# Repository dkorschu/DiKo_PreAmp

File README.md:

# $\text{-DIKO-}\sqrt{\text{REGGAE}}\text{-PREAMP-}$

[English version below](#english-version)

Dieses Repository zeigt die Entwicklung des DIKO ELEKTROTECHNIK Vorverstärkers, vom ersten Prototyp bis zum aktuellen Stand.

## Ordnerstruktur

- Blockschaltbilder
- Ältere Versionen
- KiCad Dateien
- Bilder
- Datenblätter
- 3D Druck

## Version 1

Version 1 entstand im Rahmen meiner Bachelorarbeit. Schaltpläne und Fertigungsdateien der Platinen wurden mit Altium Designer erstellt. Das Besondere an dieser Version: Die analoge Frequenzweiche lässt sich über Digitalpotentiometer einstellen.

**Hinweis: Version 1 ist fehlerhaft!**

## Version 2

Version 2 baut auf den Erkenntnissen aus Version 1 auf und bringt komplett neue Platinen mit. Die Digitalpotentiometer sind entfallen, da der Vorverstärker einfacher werden und der Fokus zunächst auf der analogen Schaltungstechnik liegen sollte. Zur Berechnung der Frequenzweiche wurden außerdem Jupyter Notebooks eingesetzt, die sehr gute Ergebnisse geliefert haben.

Bei den bisherigen Tests wurden schaltungstechnisch keine Fehler gefunden. Trotzdem gibt es zwei Schwachstellen:

- Das Platinenlayout ist nicht zufriedenstellend.
- Der Mikrofonvorverstärker verstärkt das Signal nicht ausreichend.

Aus diesen Gründen wird nun an Version 3 gearbeitet.

## Version 3

Version 3 teilt den Vorverstärker in einzelne Komponenten auf, die sich miteinander verbinden lassen.

2026_10_05 Den Anfang macht die Frequenzweiche, die sich auch eigenständig mit einem externen Mischpult nutzen lässt.

---

# English Version

This repository documents the development of the DIKO ELEKTROTECHNIK preamplifier, from the first prototype to the current state.

## Folder Structure

- Blockschaltbilder (block diagrams)
- Ältere Versionen (older versions)
- KiCad Dateien (KiCad files)
- Bilder (images)
- Datenblätter (datasheets)
- 3D Druck (3D printing)

## Version 1
Version 1 was developed as part of my bachelor's thesis. The schematics and PCB manufacturing files were created with Altium Designer. What makes this version special: the analog crossover can be adjusted using digital potentiometers.

**Note: Version 1 is faulty!**

## Version 2

Version 2 builds on the findings from Version 1 and comes with completely new PCBs. The digital potentiometers were removed to make the preamp simpler and to focus on the analog circuitry first. In addition, Jupyter Notebooks were used to calculate the crossover, with very good results.

So far, testing has not revealed any circuit errors. However, there are two weak points:

- The PCB layout is not satisfactory.
- The microphone preamp does not amplify the signal sufficiently.

For these reasons, work is now underway on Version 3.

## Version 3

Version 3 splits the preamp into individual components that can be connected to each other.

2026_10_05 The first step is the crossover, which can also be used on its own with an external mixing console.

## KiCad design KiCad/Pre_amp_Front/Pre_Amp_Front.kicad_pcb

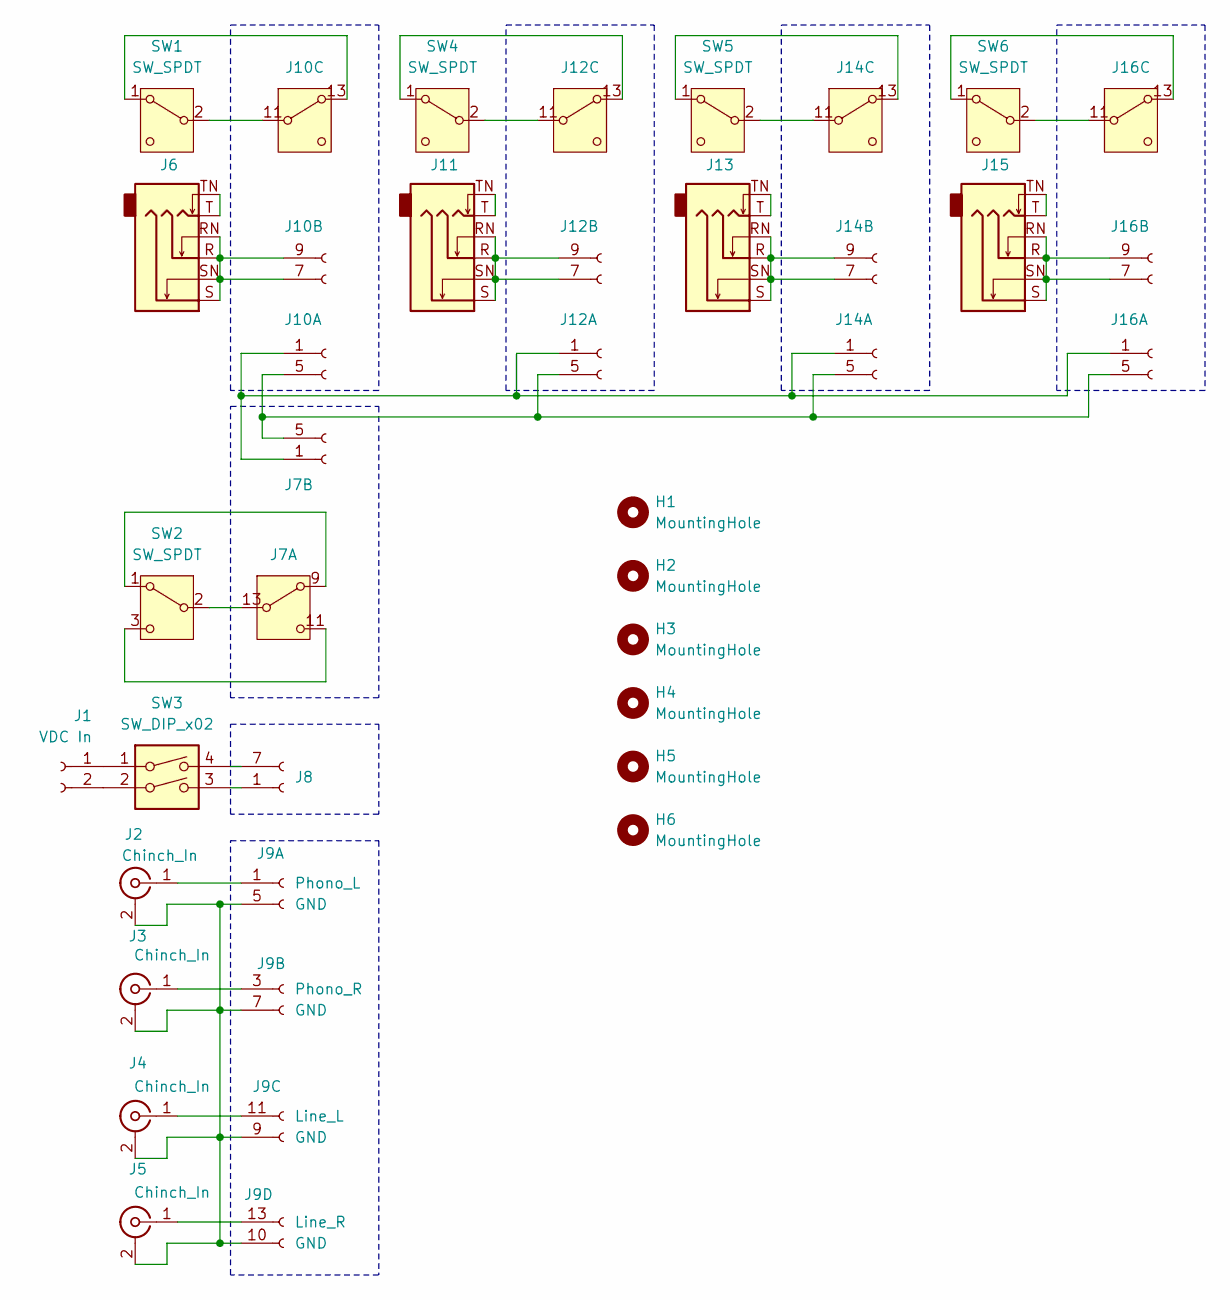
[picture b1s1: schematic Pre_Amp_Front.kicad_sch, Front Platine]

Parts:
H1, H2, H3, H4, H5, H6: MountingHole; MountingHole_3.2mm_M3
J1: VDC In; Chinch_lose
J2, J3, J4, J5: Chinch_In; Chinch_lose
J6, J11, J13, J15: NRJ6HF; Jack_6.35mm_Neutrik_NMJ6HFD3_Horizontal
J7: Stecker_1Out_Switch; PinHeader_2x07_P2.54mm_Vertical
J8: Stecker_2x7_VDC; PinHeader_2x07_P2.54mm_Vertical
J9: Stecker_4In; PinHeader_2x07_P2.54mm_Vertical
J10, J12, J14, J16: Stecker_In_Out_Switch; PinHeader_2x07_P2.54mm_Vertical
SW1, SW4, SW5, SW6: SW_SPDT; Chinch_lose
SW2: SW_SPDT; Schalter_3x_lose
SW3: SW_DIP_x02; Schalter_4x_lose

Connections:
unnamed: J1.1, SW3.1
unnamed: J1.2, SW3.2
unnamed: J2.2 (Ext), J3.2 (Ext), J4.2 (Ext), J5.2 (Ext), J9.5 (GND), J9.6 (GND), J9.7 (GND), J9.8 (GND), J9.9 (GND), J9.10 (GND)
unnamed: J2.1 (In), J9.1 (Phono_L), J9.2
unnamed: J3.1 (In), J9.3 (Phono_R), J9.4 (Phono_R)
unnamed: J4.1 (In), J9.11 (Line_L), J9.12 (Line_L)
unnamed: J5.1 (In), J9.13 (Line_R), J9.14 (Line_R)
unnamed: J6.T, J6.TN
unnamed: J7.9 (SW_In1), J7.10 (SW_2), SW2.1 (A)
unnamed: J7.11 (SW_In2), J7.12 (SW_3), SW2.3 (C)
unnamed: J8.7 (VCC_GND), J8.8 (VCC_GND), J8.9 (VCC_GND), J8.10 (VCC_GND), J8.11 (VCC_GND), J8.12 (VCC_GND), J8.13 (VCC_GND), J8.14 (VCC_GND), SW3.4
unnamed: J8.1 (VCC_In), J8.2 (VCC_In), J8.3 (VCC_In), J8.4 (VCC_In), J8.5 (VCC_In), J8.6 (VCC_In), SW3.3
unnamed: J7.1 (Out), J7.2 (Out), J10.1, J10.2, J12.1, J12.2, J14.1, J14.2, J16.1, J16.2
unnamed: J7.3 (GND), J7.4 (GND), J7.5 (GND), J7.6 (GND), J7.7 (GND), J7.8 (GND), J10.3, J10.4, J10.5, J10.6, J12.3, J12.4, J12.5, J12.6, J14.3, J14.4, J14.5, J14.6, J16.3, J16.4, J16.5, J16.6
unnamed: J6.R, J6.RN, J6.S, J6.SN, J10.7, J10.8, J10.9, J10.10
unnamed: J10.11 (SW_In), J10.12, SW1.2 (B)
unnamed: J10.13 (SW_Out), J10.14, SW1.1 (A)
unnamed: J11.T, J11.TN
unnamed: J11.R, J11.RN, J11.S, J11.SN, J12.7, J12.8, J12.9, J12.10
unnamed: J12.11 (SW_In), J12.12, SW4.2 (B)
unnamed: J12.13 (SW_Out), J12.14, SW4.1 (A)
unnamed: J13.T, J13.TN
unnamed: J13.R, J13.RN, J13.S, J13.SN, J14.7, J14.8, J14.9, J14.10
unnamed: J14.11 (SW_In), J14.12, SW5.2 (B)
unnamed: J14.13 (SW_Out), J14.14, SW5.1 (A)
unnamed: J15.T, J15.TN
unnamed: J15.R, J15.RN, J15.S, J15.SN, J16.7, J16.8, J16.9, J16.10
unnamed: J16.11 (SW_In), J16.12, SW6.2 (B)
unnamed: J16.13 (SW_Out), J16.14, SW6.1 (A)
unnamed: J7.13 (SW_Out), J7.14 (SW_Out), SW2.2 (B)

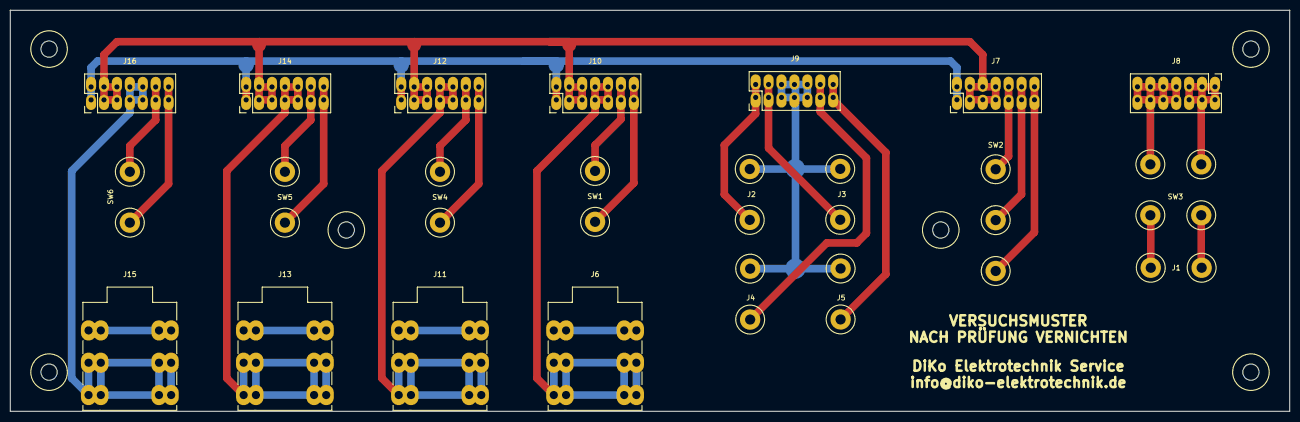
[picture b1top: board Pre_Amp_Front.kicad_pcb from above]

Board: 2 copper layers, 251.5 x 78.8 mm, 28 parts (0 on the bottom side), 30 nets.

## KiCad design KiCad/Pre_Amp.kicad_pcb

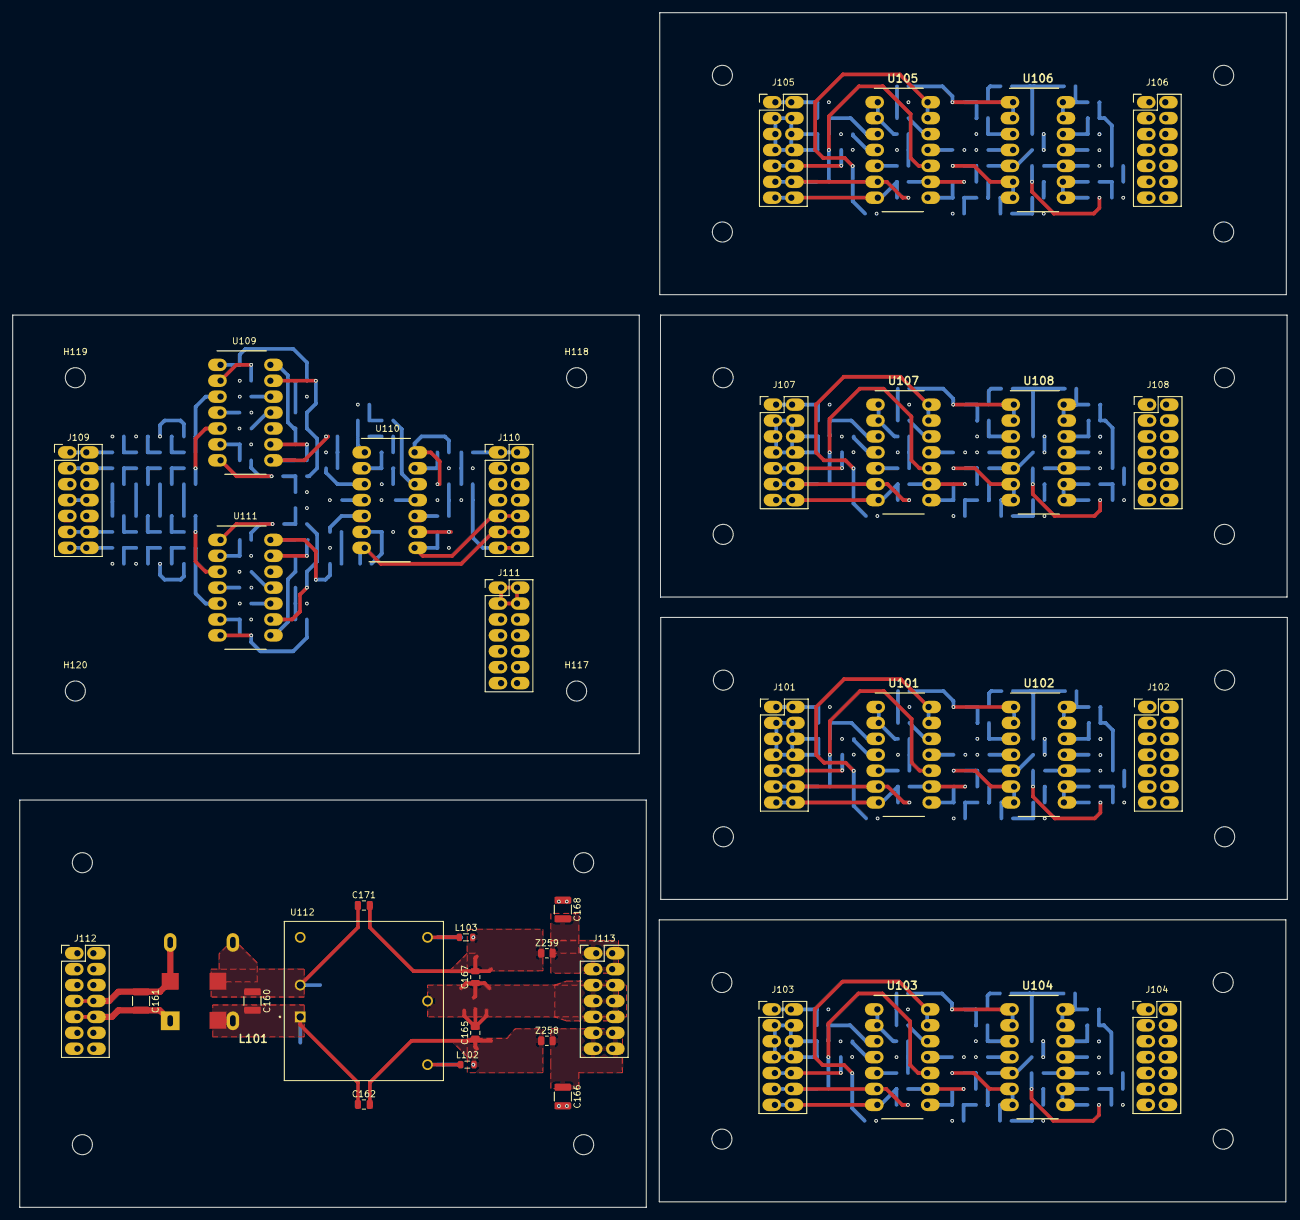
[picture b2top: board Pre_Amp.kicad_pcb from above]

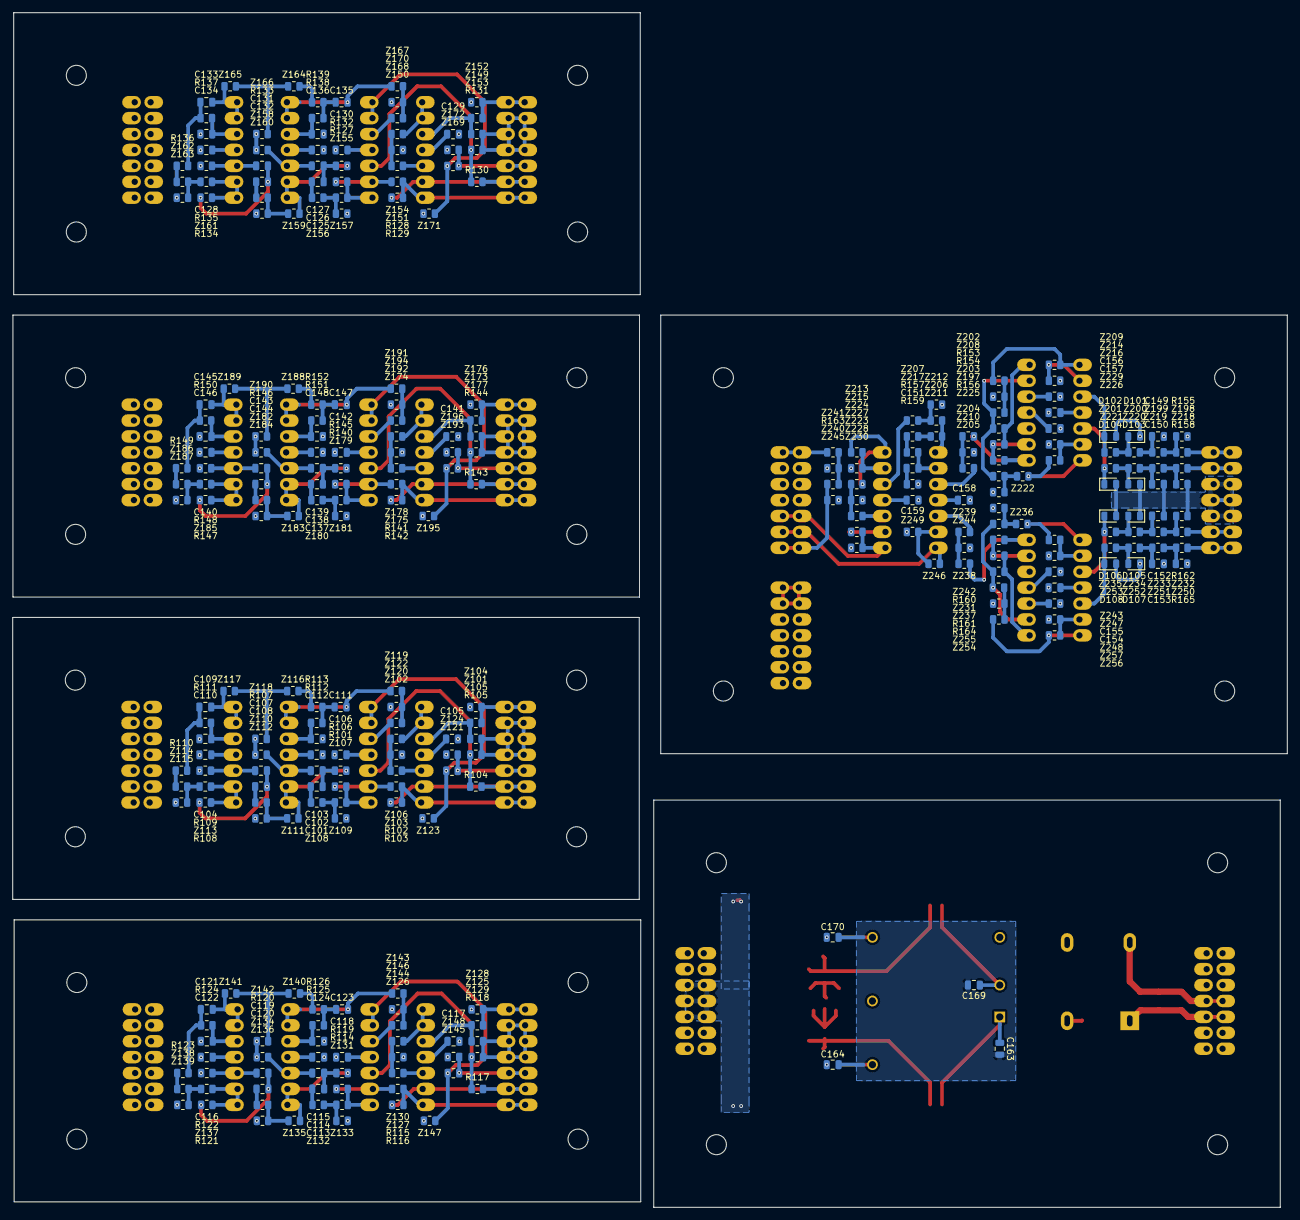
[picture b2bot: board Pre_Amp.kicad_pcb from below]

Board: 4 copper layers, 203.4 x 190.7 mm, 355 parts (293 on the bottom side), 210 nets.

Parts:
C101, C102, C113, C114, C125, C126, C137, C138, C149, C150, C152, C153, C163, C169: 10n; C_0805_2012Metric
C103, C104, C105, C106, C112, C115, C116, C117, C118, C124, C127, C128, C129, C130, C136, C139, C140, C141, C142, C148, C154, C155, C156, C157, C158, C159, C165, C167: 100n; C_0805_2012Metric
C107, C108, C119, C120, C131, C132, C143, C144: 220n; C_0805_2012Metric
C109, C110, C121, C122, C133, C134, C145, C146: 150n; C_0805_2012Metric
C111, C123, C135, C147: 1u; C_0805_2012Metric
C151: 47u; C_0805_2012Metric
C160, C161, C166, C168: 10u; C_1210_3225Metric
C162, C171: 470p; C_0805_2012Metric
C164, C170: 1n; C_0805_2012Metric
D101, D102, D103, D104, D105, D106, D107, D108: D; D_0805_2012Metric
H101, H102, H103, H104, H105, H106, H107, H108, H109, H110, H111, H112, H113, H114, H115, H116, H117, H118, H119, H120, H121, H122, H123, H124: MountingHole; MountingHole_3.2mm_M3
J101, J103, J105, J107: Stecker_In_Out_Switch; PinHeader_2x07_P2.54mm_Vertical
J102, J104, J106, J108, J111: Conn_02x07_Odd_Even; PinHeader_2x07_P2.54mm_Vertical
J109: Stecker_4In; PinHeader_2x07_P2.54mm_Vertical
J110: Stecker_1Out_Switch; PinHeader_2x07_P2.54mm_Vertical
J112: Stecker_1In_2Switch; PinHeader_2x07_P2.54mm_Vertical
J113: VCC; PinHeader_2x07_P2.54mm_Vertical
L101: WE-SL575
L102, L103: Dämpfungsperle, 220 Ohm @ 100MHz, 0.5A; L_0805_2012Metric
R101, R105, R114, R118, R127, R131, R140, R144: 100k; R_0805_2012Metric
R102, R103, R104, R115, R116, R117, R128, R129, R130, R141, R142, R143, R159: 1k; R_0805_2012Metric
R106, R119, R132, R145: 560k; R_0805_2012Metric
R107, R120, R133, R146: 680k; R_0805_2012Metric
R108, R121, R134, R147, R153, R154, R156, R160, R161, R164: 10k; R_0805_2012Metric
R109, R122, R135, R148: 75k; R_0805_2012Metric
R110, R111, R123, R124, R136, R137, R149, R150: 15k; R_0805_2012Metric
R112, R113, R125, R126, R138, R139, R151, R152: 7k5; R_0805_2012Metric
R155, R158, R162, R163, R165: 390k; R_0805_2012Metric
R157: 33k; R_0805_2012Metric
U101, U102, U103, U104, U105, U106, U107, U108, U109, U110, U111: TL074; DIP794W53P254L1930H508Q14N
U112: REC10K-2415; CONV_REC10K-2415DAW_H2
Z101, Z121, Z125, Z145, Z149, Z169, Z173, Z193: 1u; R_0805_2012Metric
Z102, Z103, Z107, Z108, Z110, Z111, Z113, Z114, Z116, Z117, Z119, Z120, Z126, Z127, Z131, Z132, Z134, Z135, Z137, Z138, Z140, Z141, Z143, Z144, Z150, Z151, Z155, Z156, Z158, Z159, Z161, Z162, Z164, Z165, Z167, Z168, Z174, Z175, Z179, Z180, Z182, Z183, Z185, Z186, Z188, Z189, Z191, Z192, Z204, Z205, Z206, Z207, Z223, Z224, Z238, Z239, Z258, Z259: 0R; R_0805_2012Metric
Z104, Z106, Z109, Z112, Z118, Z123, Z128, Z130, Z133, Z136, Z142, Z147, Z152, Z154, Z157, Z160, Z166, Z171, Z176, Z178, Z181, Z184, Z190, Z195, Z197, Z198, Z199, Z200, Z201, Z202, Z203, Z208, Z209, Z213, Z214, Z215, Z216, Z218, Z219, Z220, Z221, Z222, Z225, Z226, Z228, Z229, Z230, Z231, Z232, Z233, Z234, Z235, Z236, Z237, Z240, Z241, Z242, Z243, Z245, Z246, Z247, Z248, Z249, Z250, Z251, Z252, Z253, Z254, Z255, Z256, Z257: R_0805_2012Metric
Z105, Z124, Z129, Z148, Z153, Z172, Z177, Z196: 100k; R_0805_2012Metric
Z115, Z122, Z139, Z146, Z163, Z170, Z187, Z194, Z210, Z212, Z227, Z244: 820k; R_0805_2012Metric
Z211: 390k/10n; R_0805_2012Metric
Z217: 33k/2n2; R_0805_2012Metric

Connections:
+15V: C103.2, C105.2, C115.2, C117.2, C127.2, C129.2, C139.2, C141.2, C154.2, C156.2, C158.2, C166.1, J102.11, J102.12, J102.13, J102.14, J104.11, J104.12, J104.13, J104.14, J106.11, J106.12, J106.13, J106.14, J108.11, J108.12, J108.13, J108.14, J111.11, J111.12, J111.13, J111.14, J113.11 (+15V), J113.12 (+15V), J113.13 (+15V), J113.14 (+15V), U101.4 (V+), U102.4 (V+), U103.4 (V+), U104.4 (V+), U105.4 (V+), U106.4 (V+), U107.4 (V+), U108.4 (V+), U109.4 (V+), U110.4 (V+), U111.4 (V+), Z258.2
-15V: C104.2, C106.2, C116.2, C118.2, C128.2, C130.2, C140.2, C142.2, C155.2, C157.2, C159.2, C168.2, J102.1, J102.2, J102.3, J102.4, J104.1, J104.2, J104.3, J104.4, J106.1, J106.2, J106.3, J106.4, J108.1, J108.2, J108.3, J108.4, J111.1, J111.2, J111.3, J111.4, J113.1 (-15V), J113.2 (-15V), J113.3 (-15V), J113.4 (-15V), U101.11 (V-), U102.11 (V-), U103.11 (V-), U104.11 (V-), U105.11 (V-), U106.11 (V-), U107.11 (V-), U108.11 (V-), U109.11 (V-), U110.11 (V-), U111.11 (V-), Z259.2
GND: C103.1, C104.1, C105.1, C106.1, C110.1, C112.1, C115.1, C116.1, C117.1, C118.1, C122.1, C124.1, C127.1, C128.1, C129.1, C130.1, C134.1, C136.1, C139.1, C140.1, C141.1, C142.1, C146.1, C148.1, C149.1, C150.1, C152.1, C153.1, C154.1, C155.1, C156.1, C157.1, C158.1, C159.1, C165.2, C166.2, C167.1, C168.1, D101.1 (K), D102.2 (A), D103.1 (K), D104.2 (A), D105.1 (K), D106.2 (A), D107.1 (K), D108.2 (A), J101.3, J101.4, J101.5, J101.6, J101.7, J101.8, J102.5, J102.6, J102.7, J102.8, J102.9, J102.10, J103.3, J103.4, J103.5, J103.6, J103.7, J103.8, J104.5, J104.6, J104.7, J104.8, J104.9, J104.10, J105.3, J105.4, J105.5, J105.6, J105.7, J105.8, J106.5, J106.6, J106.7, J106.8, J106.9, J106.10, J107.3, J107.4, J107.5, J107.6, J107.7, J107.8, J108.5, J108.6, J108.7, J108.8, J108.9, J108.10, J109.5 (GND), J109.6 (GND), J109.7 (GND), J109.8 (GND), J109.9 (GND), J109.10 (GND), J110.3 (GND), J110.4 (GND), J110.5 (GND), J110.6 (GND), J110.7 (GND), J110.8 (GND), J111.5, J111.6, J111.7, J111.8, J111.9, J111.10, J113.5 (GND), J113.6 (GND), J113.7 (GND), J113.8 (GND), J113.9 (GND), J113.10 (GND), R105.1, R107.1, R109.1, R118.1, R120.1, R122.1, R131.1, R133.1, R135.1, R144.1, R146.1, R148.1, R155.2, R158.2, R159.1, R162.2, R163.2, R165.2, U109.10 (+), U111.12 (+), U112.5 (COM), Z104.2, Z105.2, Z106.2, Z109.2, Z112.2, Z115.2, Z118.2, Z122.2, Z123.2, Z124.2, Z128.2, Z129.2, Z130.2, Z133.2, Z136.2, Z139.2, Z142.2, Z146.2, Z147.2, Z148.2, Z152.2, Z153.2, Z154.2, Z157.2, Z160.2, Z163.2, Z166.2, Z170.2, Z171.2, Z172.2, Z176.2, Z177.2, Z178.2, Z181.2, Z184.2, Z187.2, Z190.2, Z194.2, Z195.2, Z196.2, Z208.2, Z210.2, Z212.2, Z214.2, Z215.2, Z216.2, Z225.2, Z227.2, Z229.2, Z230.2, Z242.2, Z244.2, Z245.2, Z247.2, Z248.2, Z249.2, Z255.2, Z257.2
GND_FILT: C163.2, C164.2, C169.2, C170.2
unnamed: C101.1, Z108.1
unnamed: C101.2, C102.1, R106.1
unnamed: C107.1, C108.2, R108.1
unnamed: C108.1, Z110.2
unnamed: C109.1, R110.2, R111.1
unnamed: C111.1, R112.1, R113.2
unnamed: C113.1, Z132.1
unnamed: C113.2, C114.1, R119.1
unnamed: C119.1, C120.2, R121.1
unnamed: C120.1, Z134.2
unnamed: C121.1, R123.2, R124.1
unnamed: C123.1, R125.1, R126.2
unnamed: C125.1, Z156.1
unnamed: C125.2, C126.1, R132.1
unnamed: C131.1, C132.2, R134.1
unnamed: C132.1, Z158.2
unnamed: C133.1, R136.2, R137.1
unnamed: C135.1, R138.1, R139.2
unnamed: C137.1, Z180.1
unnamed: C137.2, C138.1, R145.1
unnamed: C143.1, C144.2, R147.1
unnamed: C144.1, Z182.2
unnamed: C145.1, R149.2, R150.1
unnamed: C147.1, R151.1, R152.2
unnamed: C149.2, Z199.2, Z200.1
unnamed: C150.2, Z219.2, Z220.1
unnamed: C151.1, R159.2
unnamed: C152.2, Z233.2, Z234.1
unnamed: C153.2, Z251.2, Z252.1
unnamed: C161.1, J112.7 (SW_2), J112.8 (SW_2), L101.4
unnamed: C161.2, J112.9 (SW_4), J112.10 (SW_4), L101.1
unnamed: C162.2, C164.1, C165.1, L102.2, Z258.1
unnamed: C167.2, C170.1, C171.2, L103.2, Z259.1
unnamed: D101.2 (A), Z200.2, Z201.1
unnamed: D102.1 (K), U109.3 (+), Z201.2
unnamed: D103.2 (A), Z220.2, Z221.1
unnamed: D104.1 (K), U109.5 (+), Z221.2
unnamed: D105.2 (A), Z234.2, Z235.1
unnamed: D106.1 (K), U111.3 (+), Z235.2
unnamed: D107.2 (A), Z252.2, Z253.1
unnamed: D108.1 (K), U111.5 (+), Z253.2
unnamed: J101.1, J101.2, J103.1, J103.2, J105.1, J105.2, J107.1, J107.2, J110.1 (Out), J110.2 (Out), Z101.2, Z104.1, Z125.2, Z128.1, Z149.2, Z152.1, Z173.2, Z176.1, Z241.1
unnamed: J101.9, J101.10, Z121.2, Z124.1
unnamed: J101.11 (SW_In), J101.12, R103.1, R104.1, U101.6 (-)
unnamed: J101.13 (SW_Out), J101.14, R102.1, R103.2, U101.7
unnamed: J103.9, J103.10, Z145.2, Z148.1
unnamed: J103.11 (SW_In), J103.12, R116.1, R117.1, U103.6 (-)
unnamed: J103.13 (SW_Out), J103.14, R115.1, R116.2, U103.7
unnamed: J105.9, J105.10, Z169.2, Z172.1
unnamed: J105.11 (SW_In), J105.12, R129.1, R130.1, U105.6 (-)
unnamed: J105.13 (SW_Out), J105.14, R128.1, R129.2, U105.7
unnamed: J107.9, J107.10, Z193.2, Z196.1
unnamed: J107.11 (SW_In), J107.12, R142.1, R143.1, U107.6 (-)
unnamed: J107.13 (SW_Out), J107.14, R141.1, R142.2, U107.7
unnamed: J109.1 (Phono_L), J109.2, Z198.1
unnamed: J109.3 (Phono_R), J109.4 (Phono_R), Z218.1
unnamed: J109.11 (Line_L), J109.12 (Line_L), Z232.1
unnamed: J109.13 (Line_R), J109.14 (Line_R), Z250.1
unnamed: J110.9 (SW_In1), J110.10 (SW_2), U110.8, Z228.2, Z230.1
unnamed: J110.11 (SW_In2), J110.12 (SW_3), U110.7, Z246.1
unnamed: J110.13 (SW_Out), J110.14 (SW_Out), Z240.2, Z245.1
unnamed: J112.3 (VCC_GND), J112.4 (VCC_GND), J112.5 (VCC_GND), J112.6 (VCC_GND), J112.11 (SW_1), J112.12 (SW_1)
unnamed: J112.1 (VCC_In), J112.2 (VCC_In), J112.13 (SW_3), J112.14 (SW_3)
unnamed: R101.2, U101.8, Z107.2
unnamed: R110.1, Z114.1
unnamed: R113.1, Z116.2
unnamed: R114.2, U103.8, Z131.2
unnamed: R123.1, Z138.1
unnamed: R126.1, Z140.2
unnamed: R127.2, U105.8, Z155.2
unnamed: R136.1, Z162.1
unnamed: R139.1, Z164.2
unnamed: R140.2, U107.8, Z179.2
unnamed: R149.1, Z186.1
unnamed: R152.1, Z188.2
unnamed: R153.1, Z202.2, Z208.1
unnamed: R154.2, U109.14, Z203.2
unnamed: R155.1, Z198.2, Z199.1
unnamed: R156.1, Z222.2, Z225.1
unnamed: R157.1, Z217.2
unnamed: R158.1, Z218.2, Z219.1
unnamed: R160.1, Z236.2, Z242.1
unnamed: R161.2, U111.8, Z237.2
unnamed: R162.1, Z232.2, Z233.1
unnamed: R163.1, Z240.1, Z241.2
unnamed: R164.1, Z254.2, Z255.1
unnamed: R165.1, Z250.2, Z251.1
unnamed: U101.3 (+), Z101.1, Z105.1
unnamed: U101.1, U101.2 (-), Z102.2
unnamed: U101.5 (+), Z103.1
unnamed: R104.2, R105.2, U101.10 (+)
unnamed: R101.1, R102.2, U101.9 (-)
unnamed: U101.12 (+), Z120.2
unnamed: U101.13 (-), U101.14, Z121.1, Z123.1
unnamed: C112.2, R112.2, U102.3 (+)
unnamed: C111.2, U102.1, U102.2 (-), Z119.1
unnamed: C102.2, R107.2, U102.5 (+)
unnamed: R106.2, U102.6 (-), U102.7, Z111.1
unnamed: C107.2, R109.2, U102.10 (+)
unnamed: R108.2, U102.8, U102.9 (-), Z113.2
unnamed: C110.2, R111.2, U102.12 (+)
unnamed: C109.2, U102.13 (-), U102.14, Z117.1
unnamed: U103.3 (+), Z125.1, Z129.1
unnamed: U103.1, U103.2 (-), Z126.2
unnamed: U103.5 (+), Z127.1
unnamed: R117.2, R118.2, U103.10 (+)
unnamed: R114.1, R115.2, U103.9 (-)
unnamed: U103.12 (+), Z144.2
unnamed: U103.13 (-), U103.14, Z145.1, Z147.1
unnamed: C124.2, R125.2, U104.3 (+)
unnamed: C123.2, U104.1, U104.2 (-), Z143.1
unnamed: C114.2, R120.2, U104.5 (+)
unnamed: R119.2, U104.6 (-), U104.7, Z135.1
unnamed: C119.2, R122.2, U104.10 (+)
unnamed: R121.2, U104.8, U104.9 (-), Z137.2
unnamed: C122.2, R124.2, U104.12 (+)
unnamed: C121.2, U104.13 (-), U104.14, Z141.1
unnamed: U105.3 (+), Z149.1, Z153.1
unnamed: U105.1, U105.2 (-), Z150.2
unnamed: U105.5 (+), Z151.1
unnamed: R130.2, R131.2, U105.10 (+)
unnamed: R127.1, R128.2, U105.9 (-)
unnamed: U105.12 (+), Z168.2
unnamed: U105.13 (-), U105.14, Z169.1, Z171.1
unnamed: C136.2, R138.2, U106.3 (+)
unnamed: C135.2, U106.1, U106.2 (-), Z167.1
unnamed: C126.2, R133.2, U106.5 (+)
unnamed: R132.2, U106.6 (-), U106.7, Z159.1
unnamed: C131.2, R135.2, U106.10 (+)
unnamed: R134.2, U106.8, U106.9 (-), Z161.2
unnamed: C134.2, R137.2, U106.12 (+)
unnamed: C133.2, U106.13 (-), U106.14, Z165.1
unnamed: U107.3 (+), Z173.1, Z177.1
unnamed: U107.1, U107.2 (-), Z174.2
unnamed: U107.5 (+), Z175.1
unnamed: R143.2, R144.2, U107.10 (+)
unnamed: R140.1, R141.2, U107.9 (-)
unnamed: U107.12 (+), Z192.2
unnamed: U107.13 (-), U107.14, Z193.1, Z195.1
unnamed: C148.2, R151.2, U108.3 (+)
unnamed: C147.2, U108.1, U108.2 (-), Z191.1
unnamed: C138.2, R146.2, U108.5 (+)
unnamed: R145.2, U108.6 (-), U108.7, Z183.1
unnamed: C143.2, R148.2, U108.10 (+)
unnamed: R147.2, U108.8, U108.9 (-), Z185.2
unnamed: C146.2, R150.2, U108.12 (+)
unnamed: C145.2, U108.13 (-), U108.14, Z189.1
unnamed: U109.1, Z202.1, Z209.1
unnamed: U109.7, Z222.1, Z226.1
unnamed: U109.8, Z197.1, Z204.1
unnamed: U109.2 (-), Z209.2, Z214.1
unnamed: U109.6 (-), Z226.2, Z229.1
unnamed: U109.9 (-), Z197.2, Z203.1
unnamed: U109.12 (+), Z216.1
unnamed: R153.2, R154.1, R156.2, U109.13 (-)
unnamed: U110.1, Z206.1, Z211.1
unnamed: U110.14, Z213.1, Z224.1
unnamed: U110.3 (+), Z205.2
unnamed: C151.2, R157.2, U110.2 (-)
unnamed: U110.5 (+), Z239.2
unnamed: U110.6 (-), Z246.2, Z249.1
unnamed: U110.10 (+), Z223.2
unnamed: U110.9 (-), Z228.1
unnamed: U110.12 (+), Z207.2
unnamed: U110.13 (-), Z213.2, Z215.1
unnamed: U111.1, Z236.1, Z243.1
unnamed: U111.7, Z254.1, Z256.1
unnamed: U111.14, Z231.1, Z238.1
unnamed: U111.2 (-), Z243.2, Z247.1
unnamed: U111.6 (-), Z256.2, Z257.1
unnamed: U111.10 (+), Z248.1
unnamed: R160.2, R161.1, R164.2, U111.9 (-)
unnamed: U111.13 (-), Z231.2, Z237.1
unnamed: C160.2, C162.1, C163.1, L101.2, U112.1 (+VIN)
unnamed: L102.1, U112.6 (+VOUT)
unnamed: C160.1, C169.1, C171.1, L101.3, U112.2 (-VIN)
unnamed: L103.1, U112.4 (-VOUT)
unnamed: Z102.1, Z103.2, Z106.1
unnamed: Z107.1, Z108.2, Z109.1
unnamed: Z110.1, Z111.2, Z112.1
unnamed: Z113.1, Z114.2, Z115.1
unnamed: Z116.1, Z117.2, Z118.1
unnamed: Z119.2, Z120.1, Z122.1
unnamed: Z126.1, Z127.2, Z130.1
unnamed: Z131.1, Z132.2, Z133.1
unnamed: Z134.1, Z135.2, Z136.1
unnamed: Z137.1, Z138.2, Z139.1
unnamed: Z140.1, Z141.2, Z142.1
unnamed: Z143.2, Z144.1, Z146.1
unnamed: Z150.1, Z151.2, Z154.1
unnamed: Z155.1, Z156.2, Z157.1
unnamed: Z158.1, Z159.2, Z160.1
unnamed: Z161.1, Z162.2, Z163.1
unnamed: Z164.1, Z165.2, Z166.1
unnamed: Z167.2, Z168.1, Z170.1
unnamed: Z174.1, Z175.2, Z178.1
unnamed: Z179.1, Z180.2, Z181.1
unnamed: Z182.1, Z183.2, Z184.1
unnamed: Z185.1, Z186.2, Z187.1
unnamed: Z188.1, Z189.2, Z190.1
unnamed: Z191.2, Z192.1, Z194.1
unnamed: Z204.2, Z205.1, Z210.1
unnamed: Z206.2, Z207.1, Z212.1
unnamed: Z211.2, Z217.1
unnamed: Z223.1, Z224.2, Z227.1
unnamed: Z238.2, Z239.1, Z244.1

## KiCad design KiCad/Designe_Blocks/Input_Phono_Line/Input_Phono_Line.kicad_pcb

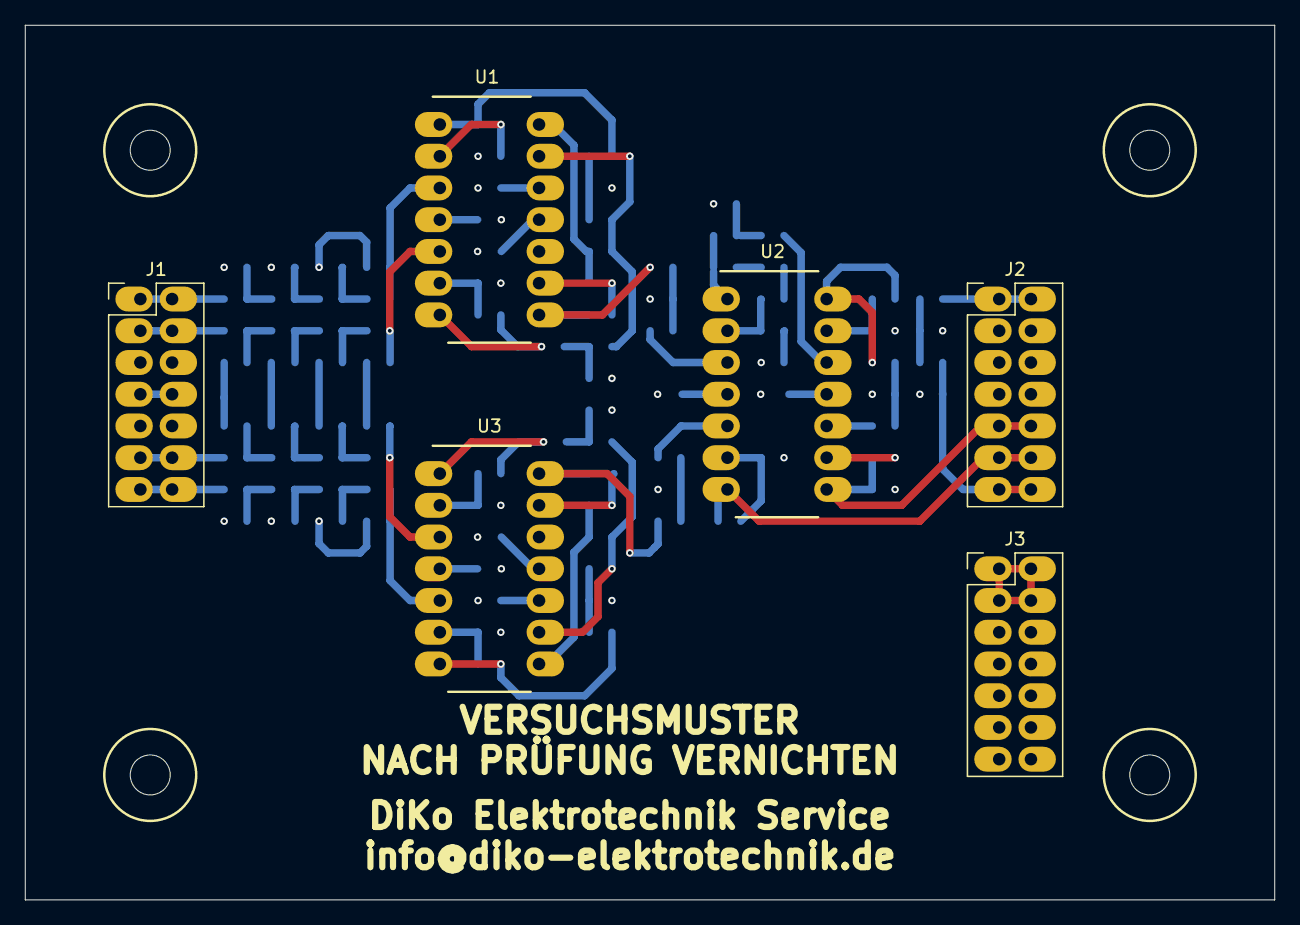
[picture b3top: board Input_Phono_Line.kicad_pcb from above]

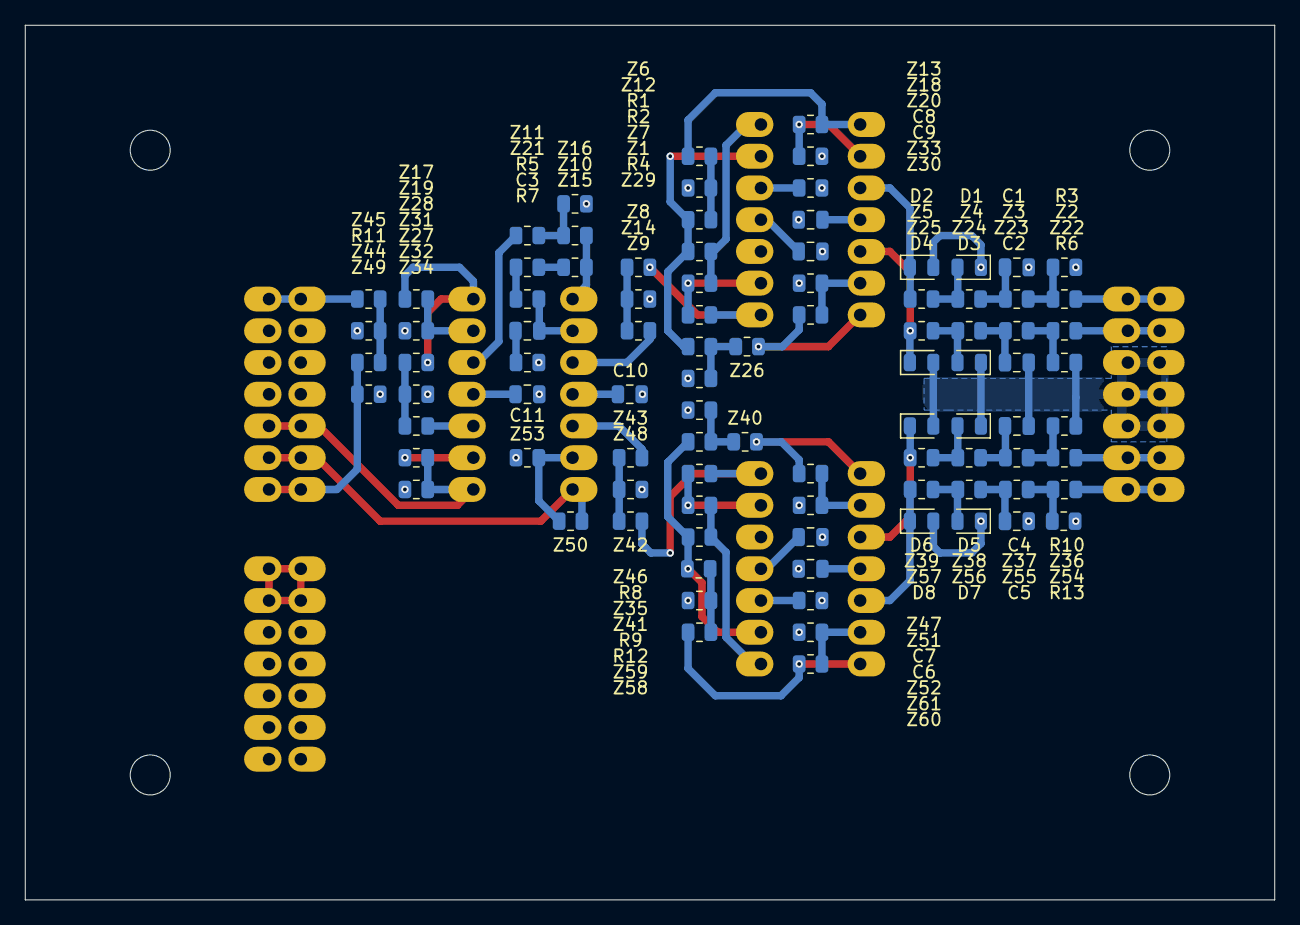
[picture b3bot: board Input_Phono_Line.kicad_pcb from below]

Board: 4 copper layers, 100.0 x 70.0 mm, 103 parts (93 on the bottom side), 67 nets.

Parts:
C1, C2, C4, C5: 10n; C_0805_2012Metric
C3: 47u; C_0805_2012Metric
C6, C7, C8, C9, C10, C11: 100n; C_0805_2012Metric
D1, D2, D3, D4, D5, D6, D7, D8: D; D_0805_2012Metric
H1, H2, H3, H4: MountingHole; MountingHole_3.2mm_M3
J1: Stecker_4In; PinHeader_2x07_P2.54mm_Vertical
J2: Stecker_1Out_Switch; PinHeader_2x07_P2.54mm_Vertical
J3: Conn_02x07_Odd_Even; PinHeader_2x07_P2.54mm_Vertical
R1, R2, R4, R8, R9, R12: 10k; R_0805_2012Metric
R3, R6, R10, R11, R13: 390k; R_0805_2012Metric
R5: 33k; R_0805_2012Metric
R7: 1k; R_0805_2012Metric
U1, U2, U3: TL074; DIP794W53P254L1930H508Q14N
Z1, Z2, Z3, Z4, Z5, Z6, Z7, Z12, Z13, Z17, Z18, Z19, Z20, Z22, Z23, Z24, Z25, Z26, Z29, Z30, Z32, Z33, Z34, Z35, Z36, Z37, Z38, Z39, Z40, Z41, Z44, Z45, Z46, Z47, Z49, Z50, Z51, Z52, Z53, Z54, Z55, Z56, Z57, Z58, Z59, Z60, Z61: R_0805_2012Metric
Z8, Z9, Z10, Z11, Z27, Z28, Z42, Z43: 0R; R_0805_2012Metric
Z14, Z16, Z31, Z48: 820k; R_0805_2012Metric
Z15: 390k/10n; R_0805_2012Metric
Z21: 33k/2n2; R_0805_2012Metric

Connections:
+15V: C6.2, C8.2, C10.2, J3.11, J3.12, J3.13, J3.14, U1.4 (V+), U2.4 (V+), U3.4 (V+)
-15V: C7.2, C9.2, C11.2, J3.1, J3.2, J3.3, J3.4, U1.11 (V-), U2.11 (V-), U3.11 (V-)
GND: C1.1, C2.1, C4.1, C5.1, C6.1, C7.1, C8.1, C9.1, C10.1, C11.1, D1.1 (K), D2.2 (A), D3.1 (K), D4.2 (A), D5.1 (K), D6.2 (A), D7.1 (K), D8.2 (A), J1.5 (GND), J1.6 (GND), J1.7 (GND), J1.8 (GND), J1.9 (GND), J1.10 (GND), J2.3 (GND), J2.4 (GND), J2.5 (GND), J2.6 (GND), J2.7 (GND), J2.8 (GND), J3.5, J3.6, J3.7, J3.8, J3.9, J3.10, R3.2, R6.2, R7.1, R10.2, R11.2, R13.2, U1.10 (+), U3.12 (+), Z12.2, Z14.2, Z16.2, Z18.2, Z19.2, Z20.2, Z29.2, Z31.2, Z33.2, Z34.2, Z46.2, Z48.2, Z49.2, Z51.2, Z52.2, Z53.2, Z59.2, Z61.2
unnamed: C1.2, Z3.2, Z4.1
unnamed: C2.2, Z23.2, Z24.1
unnamed: C3.1, R7.2
unnamed: C4.2, Z37.2, Z38.1
unnamed: C5.2, Z55.2, Z56.1
unnamed: D1.2 (A), Z4.2, Z5.1
unnamed: D2.1 (K), U1.3 (+), Z5.2
unnamed: D3.2 (A), Z24.2, Z25.1
unnamed: D4.1 (K), U1.5 (+), Z25.2
unnamed: D5.2 (A), Z38.2, Z39.1
unnamed: D6.1 (K), U3.3 (+), Z39.2
unnamed: D7.2 (A), Z56.2, Z57.1
unnamed: D8.1 (K), U3.5 (+), Z57.2
unnamed: J1.1 (Phono_L), J1.2, Z2.1
unnamed: J1.3 (Phono_R), J1.4 (Phono_R), Z22.1
unnamed: J1.11 (Line_L), J1.12 (Line_L), Z36.1
unnamed: J1.13 (Line_R), J1.14 (Line_R), Z54.1
unnamed: J2.9 (SW_In1), J2.10 (SW_2), U2.8, Z32.2, Z34.1
unnamed: J2.11 (SW_In2), J2.12 (SW_3), U2.7, Z50.1
unnamed: J2.13 (SW_Out), J2.14 (SW_Out), Z44.2, Z49.1
unnamed: J2.1 (Out), J2.2 (Out), Z45.1
unnamed: R1.1, Z6.2, Z12.1
unnamed: R2.2, U1.14, Z7.2
unnamed: R3.1, Z2.2, Z3.1
unnamed: R4.1, Z26.2, Z29.1
unnamed: R5.1, Z21.2
unnamed: R6.1, Z22.2, Z23.1
unnamed: R8.1, Z40.2, Z46.1
unnamed: R9.2, U3.8, Z41.2
unnamed: R10.1, Z36.2, Z37.1
unnamed: R11.1, Z44.1, Z45.2
unnamed: R12.1, Z58.2, Z59.1
unnamed: R13.1, Z54.2, Z55.1
unnamed: U1.1, Z6.1, Z13.1
unnamed: U1.7, Z26.1, Z30.1
unnamed: U1.8, Z1.1, Z8.1
unnamed: U1.2 (-), Z13.2, Z18.1
unnamed: U1.6 (-), Z30.2, Z33.1
unnamed: U1.9 (-), Z1.2, Z7.1
unnamed: U1.12 (+), Z20.1
unnamed: R1.2, R2.1, R4.2, U1.13 (-)
unnamed: U2.1, Z10.1, Z15.1
unnamed: U2.14, Z17.1, Z28.1
unnamed: U2.3 (+), Z9.2
unnamed: C3.2, R5.2, U2.2 (-)
unnamed: U2.5 (+), Z43.2
unnamed: U2.6 (-), Z50.2, Z53.1
unnamed: U2.10 (+), Z27.2
unnamed: U2.9 (-), Z32.1
unnamed: U2.12 (+), Z11.2
unnamed: U2.13 (-), Z17.2, Z19.1
unnamed: U3.1, Z40.1, Z47.1
unnamed: U3.7, Z58.1, Z60.1
unnamed: U3.14, Z35.1, Z42.1
unnamed: U3.2 (-), Z47.2, Z51.1
unnamed: U3.6 (-), Z60.2, Z61.1
unnamed: U3.10 (+), Z52.1
unnamed: R8.2, R9.1, R12.2, U3.9 (-)
unnamed: U3.13 (-), Z35.2, Z41.1
unnamed: Z10.2, Z11.1, Z16.1
unnamed: Z8.2, Z9.1, Z14.1
unnamed: Z15.2, Z21.1
unnamed: Z27.1, Z28.2, Z31.1
unnamed: Z42.2, Z43.1, Z48.1
